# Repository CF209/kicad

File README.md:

<pre>
This repository is for backing up and sharing my PCB designs done in KICAD

ESP8266_Water_Sensor
	- This PCB uses an ESP8266 to make an IOT device with 3 functions:
		1) Reads the resistance from a water level sensor to determine how full a water tank is
		2) Has a header to connect an MPU6050 accelerometer
		3) Can control WS2811 light strips
	- The PCB is powered by 12V and uses a buck converter to step it down to 3.3V for the ESP8266 and the MPU6050
	- The ESP8266 communicates to Home Assistant running on a Raspberry Pi over WIFI
	- Designed to fit in the 1551TFLGY plastic enclosure

ESP32_12v_Relay
	- This PCB uses an ESP32 to make an IOT device
	- The board uses MOSFETs to switch on and off 12V power to up to 4 devices
	- Designed to control lights and solenoids, but can be used for other functions as well
	- MOSFETS can be controlled by hardware PWM outputs from the ESP32
	- The PCB is powered by 12V and uses a buck converter to step it down to 3.3V for the ESP32
	- The ESP32 communicates to Home Assistant running on a Raspberry Pi over WIFI
	- Designed to fit in the 1551TFLGY plastic enclosure
</pre>

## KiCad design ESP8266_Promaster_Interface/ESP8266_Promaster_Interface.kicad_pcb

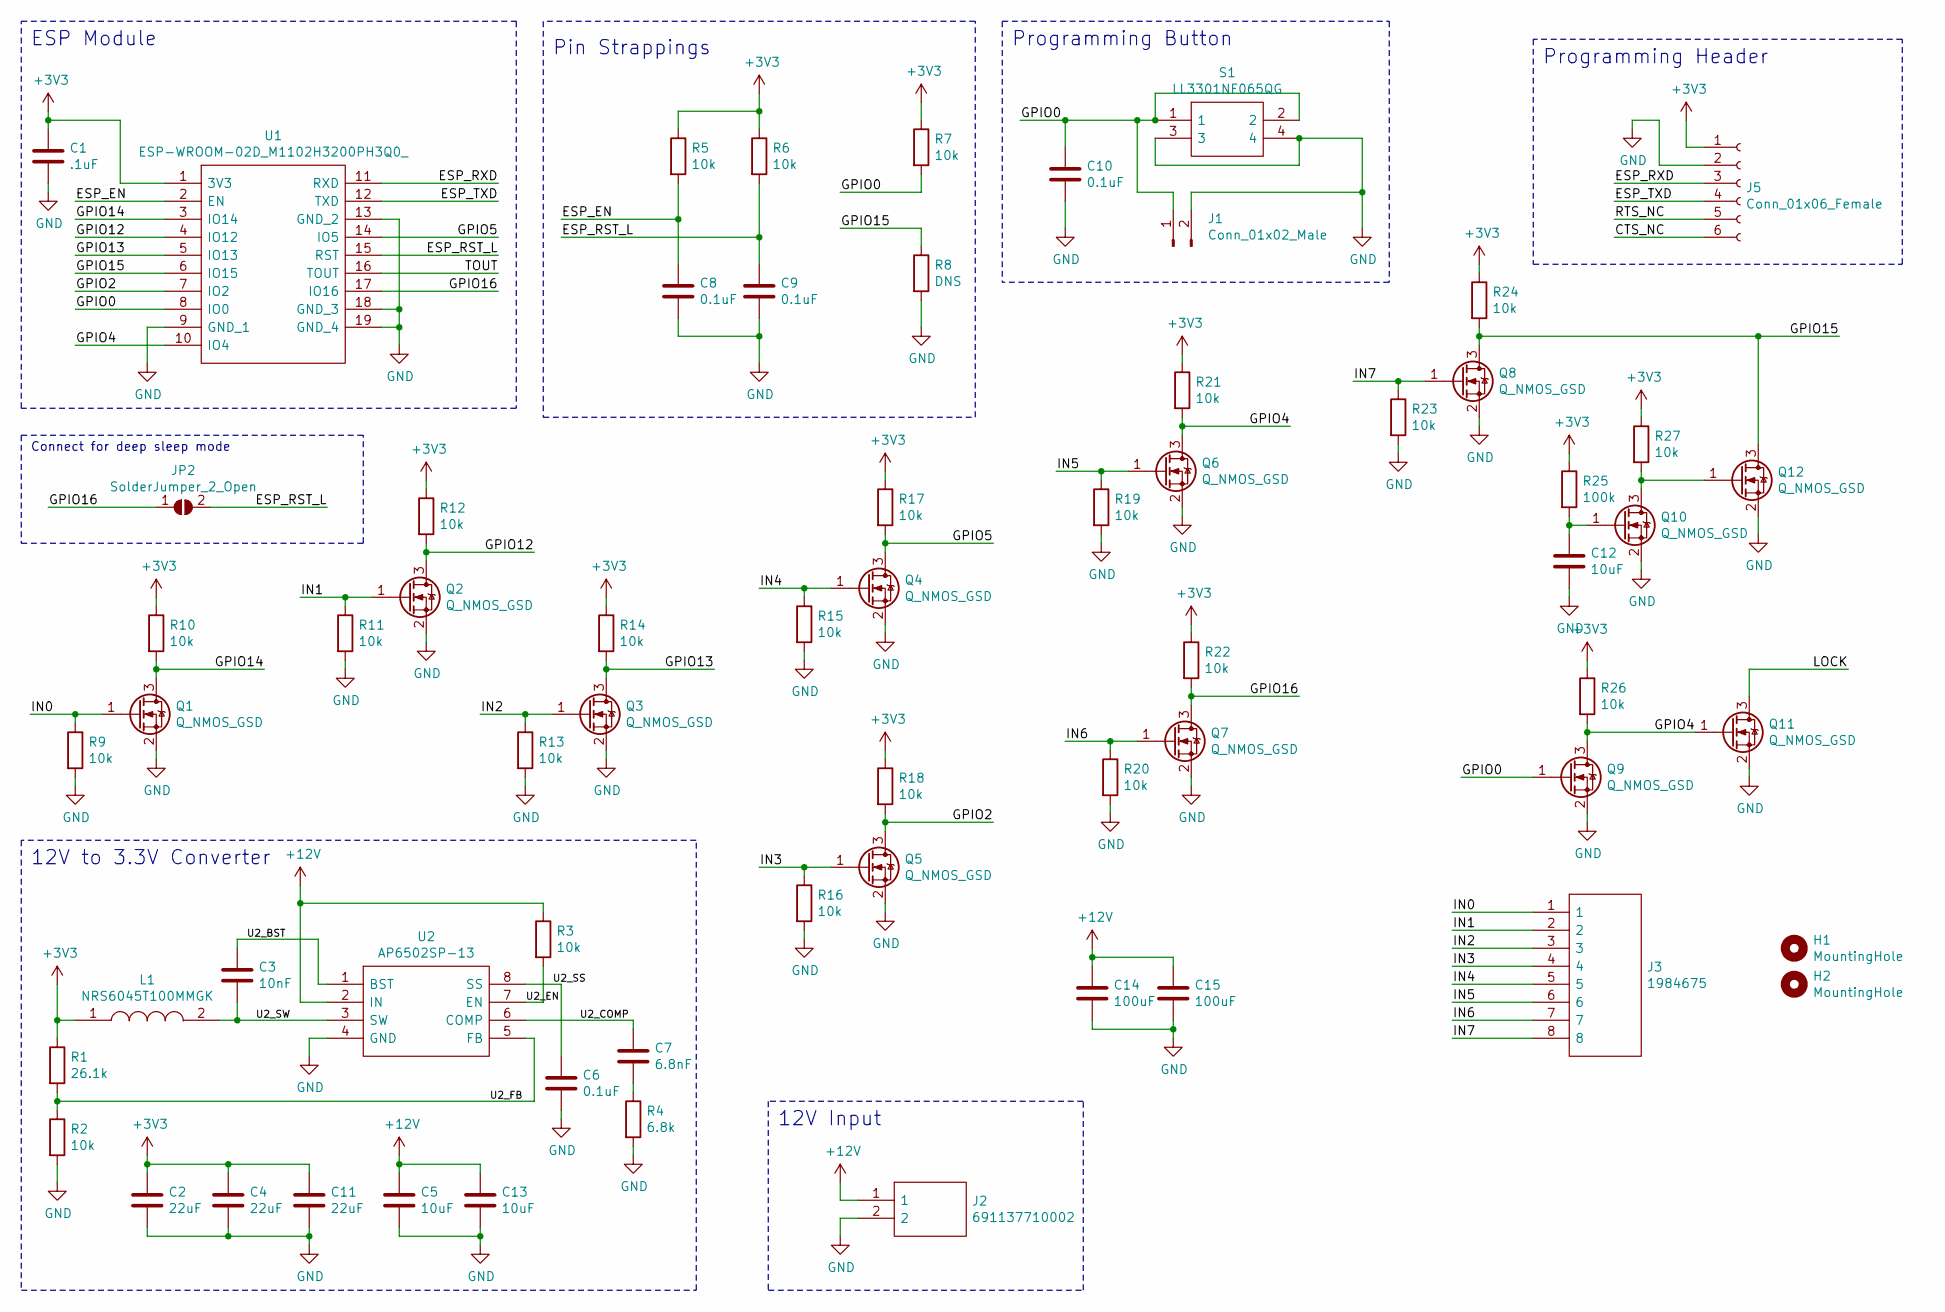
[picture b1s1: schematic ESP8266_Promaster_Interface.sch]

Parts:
C1: .1uF; C_0805_2012Metric_Pad1.18x1.45mm_HandSolder
C2, C4, C11: 22uF; C_0805_2012Metric_Pad1.18x1.45mm_HandSolder
C3: 10nF; C_0805_2012Metric_Pad1.18x1.45mm_HandSolder
C5, C12, C13: 10uF; C_0805_2012Metric_Pad1.18x1.45mm_HandSolder
C6, C8, C9, C10: 0.1uF; C_0805_2012Metric_Pad1.18x1.45mm_HandSolder
C7: 6.8nF; C_0805_2012Metric_Pad1.18x1.45mm_HandSolder
C14, C15: 100uF; CP_Radial_D6.3mm_P2.50mm
H1, H2: MountingHole; MountingHole_2.7mm_M2.5
J1: Conn_01x02_Male; PinHeader_1x02_P2.54mm_Vertical
J2: 691137710002; SHDR2W70P0X500_1X2_1000X750X1160P; Mouser Part Number 710-691137710002
J3: 1984675; Mouser Part Number 651-1984675
J5: Conn_01x06_Female; PinHeader_1x06_P2.54mm_Vertical
JP2: SolderJumper_2_Open; SolderJumper-2_P1.3mm_Open_RoundedPad1.0x1.5mm
L1: NRS6045T100MMGK; NRS6045T101MMGKV; Mouser Part Number 963-NRS6045T100MMGK
Q1, Q2, Q3, Q4, Q5, Q6, Q7, Q8, Q9, Q10, Q11, Q12: Q_NMOS_GSD; SOT-23_Handsoldering
R1: 26.1k; R_0805_2012Metric_Pad1.20x1.40mm_HandSolder
R2, R3, R5, R6, R7, R9, R10, R11, R12, R13, R14, R15, R16, R17, R18, R19, R20, R21, R22, R23, R24, R26, R27: 10k; R_0805_2012Metric_Pad1.20x1.40mm_HandSolder
R4: 6.8k; R_0805_2012Metric_Pad1.20x1.40mm_HandSolder
R8: DNS; R_0805_2012Metric_Pad1.20x1.40mm_HandSolder
R25: 100k; R_0805_2012Metric_Pad1.20x1.40mm_HandSolder
S1: LL3301NF065QG; Mouser Part Number 612-LL3301NF065QG
U1: ESP-WROOM-02D_M1102H3200PH3Q0_; ESPWROOM02DM1102H3200PH3Q0; Mouser Part Number 356-ESPWROOM02D(4MB)
U2: AP6502SP-13; SOIC127P600X150-8N; Mouser Part Number 621-AP6502SP-13

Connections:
+3V3: C1.1, C2.1, C4.1, C11.1, J5.1, L1.1, R1.1, R5.1, R6.1, R7.1, R10.1, R12.1, R14.1, R17.1, R18.1, R21.1, R22.1, R24.1, R25.1, R26.1, R27.1, U1.1 (3V3)
+12V: C5.1, C13.1, C14.1, C15.1, J2.1, R3.1, U2.2 (IN)
/CTS_NC: J5.6
/ESP_EN: C8.1, R5.2, U1.2 (EN)
/ESP_RST_L: C9.1, JP2.2 (B), R6.2, U1.15 (RST)
/ESP_RXD: J5.3, U1.11 (RXD)
/ESP_TXD: J5.4, U1.12 (TXD)
/GPIO0: C10.1, J1.1, Q9.1 (G), R7.2, S1.1, S1.2, U1.8 (IO0)
/GPIO2: Q5.3 (D), R18.2, U1.7 (IO2)
/GPIO4: Q6.3 (D), Q9.3 (D), Q11.1 (G), R21.2, R26.2, U1.10 (IO4)
/GPIO5: Q4.3 (D), R17.2, U1.14 (IO5)
/GPIO12: Q2.3 (D), R12.2, U1.4 (IO12)
/GPIO13: Q3.3 (D), R14.2, U1.5 (IO13)
/GPIO14: Q1.3 (D), R10.2, U1.3 (IO14)
/GPIO15: Q8.3 (D), Q12.3 (D), R8.1, R24.2, U1.6 (IO15)
/GPIO16: JP2.1 (A), Q7.3 (D), R22.2, U1.17 (IO16)
/IN0: J3.1, Q1.1 (G), R9.1
/IN1: J3.2, Q2.1 (G), R11.1
/IN2: J3.3, Q3.1 (G), R13.1
/IN3: J3.4, Q5.1 (G), R16.1
/IN4: J3.5, Q4.1 (G), R15.1
/IN5: J3.6, Q6.1 (G), R19.1
/IN6: J3.7, Q7.1 (G), R20.1
/IN7: J3.8, Q8.1 (G), R23.1
/LOCK: Q11.3 (D)
/RTS_NC: J5.5
/TOUT: U1.16 (TOUT)
/U2_BST: C3.1, U2.1 (BST)
/U2_COMP: C7.1, U2.6 (COMP)
/U2_EN: R3.2, U2.7 (EN)
/U2_FB: R1.2, R2.1, U2.5 (FB)
/U2_SS: C6.1, U2.8 (SS)
/U2_SW: C3.2, L1.2, U2.3 (SW)
GND: C1.2, C2.2, C4.2, C5.2, C6.2, C8.2, C9.2, C10.2, C11.2, C12.2, C13.2, C14.2, C15.2, J1.2, J2.2, J5.2, Q1.2 (S), Q2.2 (S), Q3.2 (S), Q4.2 (S), Q5.2 (S), Q6.2 (S), Q7.2 (S), Q8.2 (S), Q9.2 (S), Q10.2 (S), Q11.2 (S), Q12.2 (S), R2.2, R4.2, R8.2, R9.2, R11.2, R13.2, R15.2, R16.2, R19.2, R20.2, R23.2, S1.3, S1.4, U1.9 (GND_1), U1.13 (GND_2), U1.18 (GND_3), U1.19 (GND_4), U2.4 (GND)
unnamed: C7.2, R4.1
unnamed: C12.1, Q10.1 (G), R25.2
unnamed: Q10.3 (D), Q12.1 (G), R27.2

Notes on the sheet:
Pin Strappings
Programming Button
Programming Header
12V Input
Connect for deep sleep mode
12V to 3.3V Converter
ESP Module

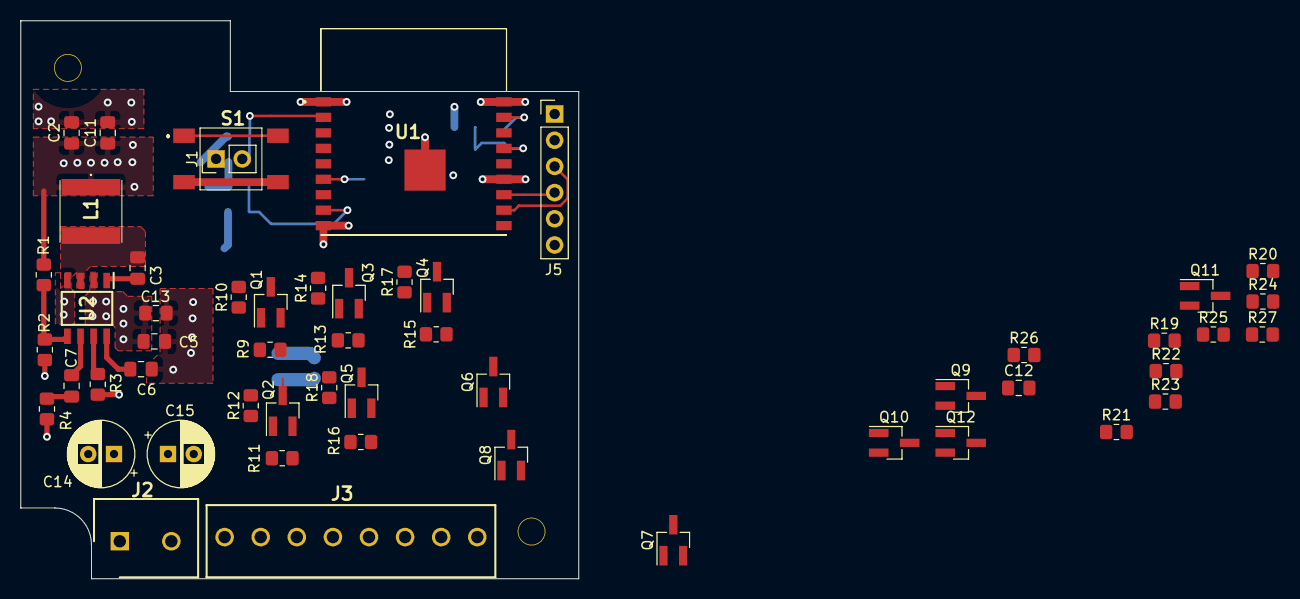
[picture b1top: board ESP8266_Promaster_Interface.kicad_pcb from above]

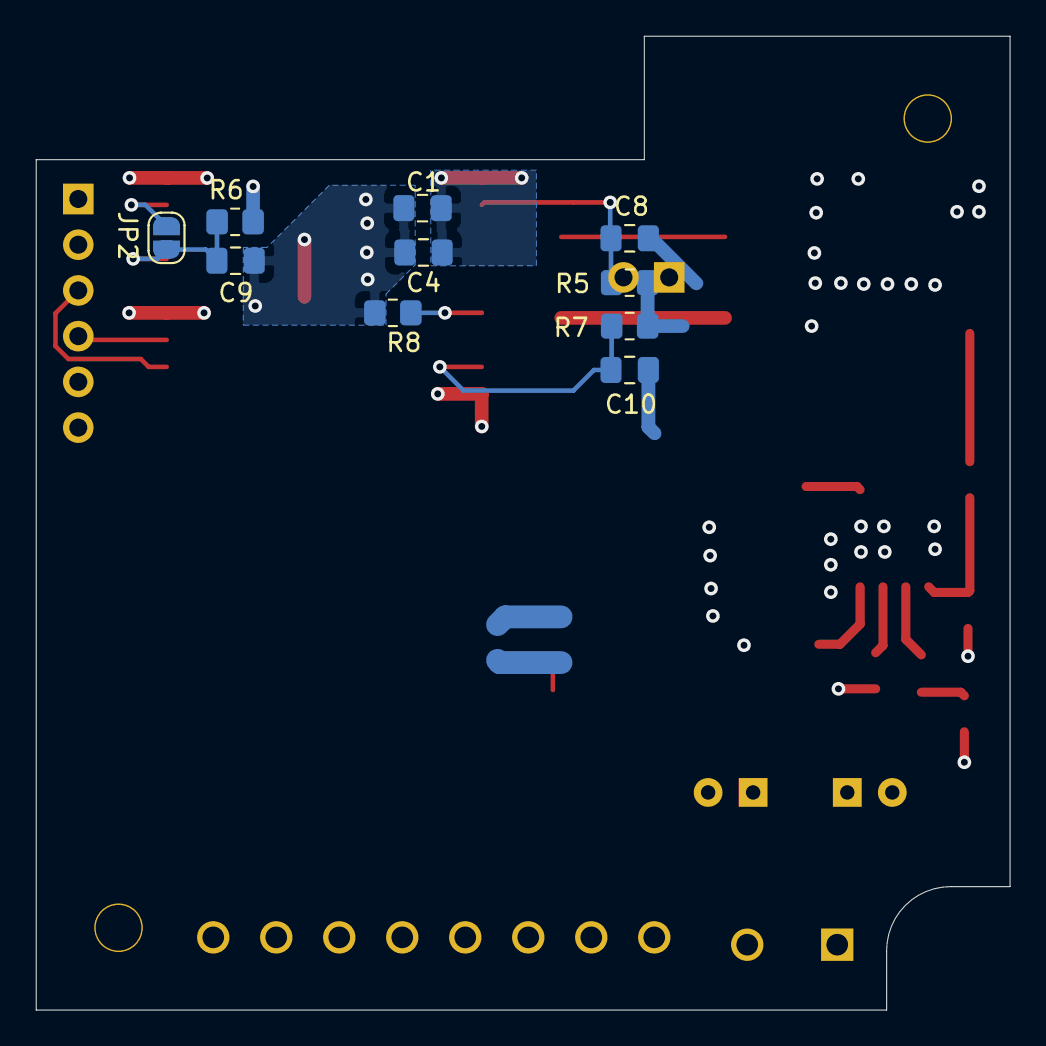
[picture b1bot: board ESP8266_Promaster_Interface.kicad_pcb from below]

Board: 4 copper layers, 54.1 x 54.1 mm, 65 parts (10 on the bottom side), 33 nets.

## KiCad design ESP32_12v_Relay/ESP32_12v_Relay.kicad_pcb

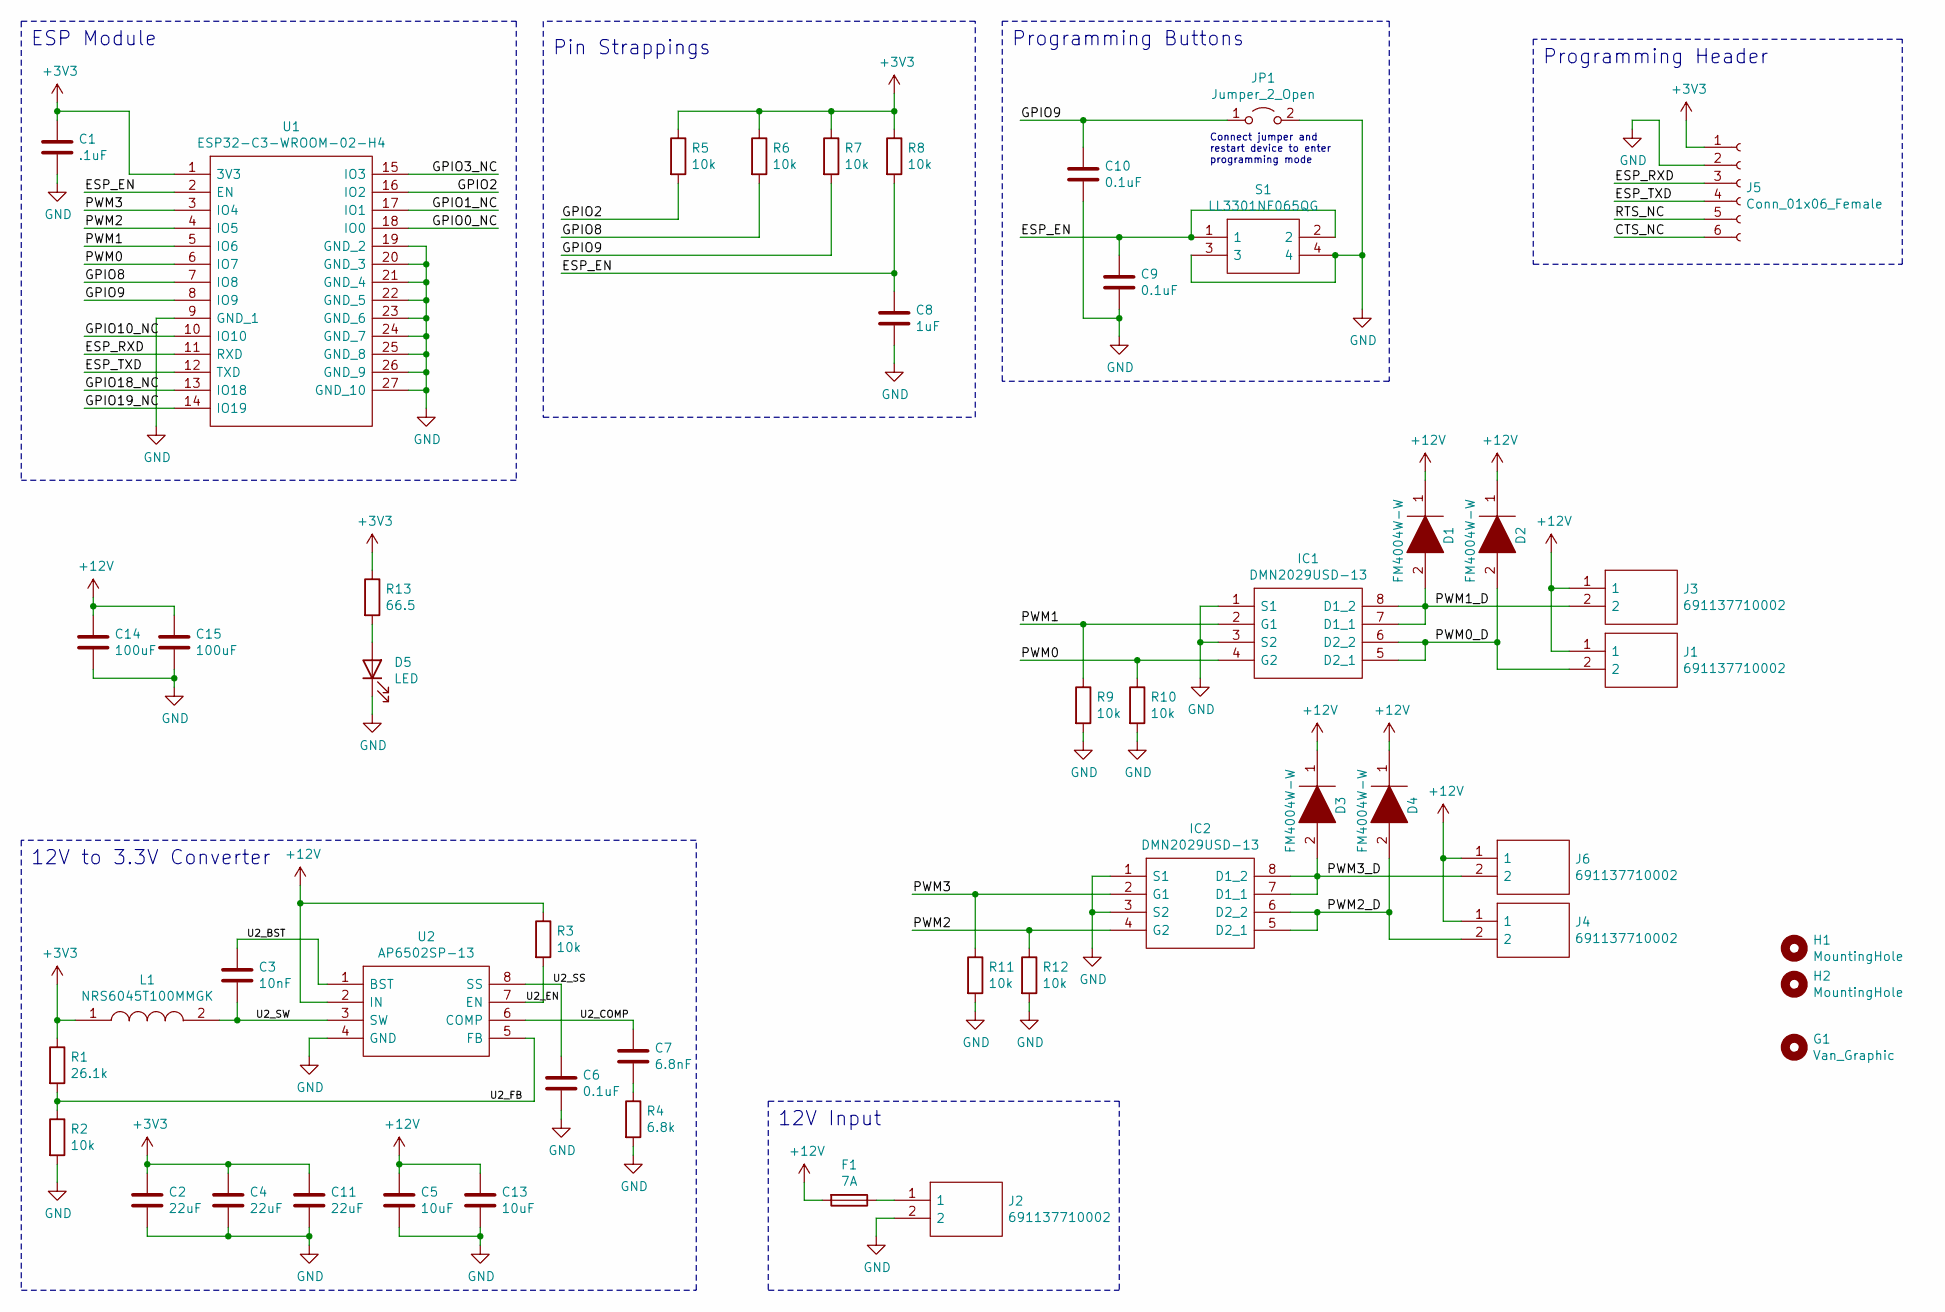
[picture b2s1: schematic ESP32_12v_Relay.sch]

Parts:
C1: .1uF; C_0805_2012Metric_Pad1.18x1.45mm_HandSolder
C2, C4, C11: 22uF; C_0805_2012Metric_Pad1.18x1.45mm_HandSolder
C3: 10nF; C_0805_2012Metric_Pad1.18x1.45mm_HandSolder
C5, C13: 10uF; C_0805_2012Metric_Pad1.18x1.45mm_HandSolder
C6, C9, C10: 0.1uF; C_0805_2012Metric_Pad1.18x1.45mm_HandSolder
C7: 6.8nF; C_0805_2012Metric_Pad1.18x1.45mm_HandSolder
C8: 1uF; C_0805_2012Metric_Pad1.18x1.45mm_HandSolder
C14, C15: 100uF; CP_Radial_D6.3mm_P2.50mm
D1, D2, D3, D4: FM4004W-W; DIOM5025X231N; Mouser Part Number 583-FM4004W-W
D5: LED; LED_0805_2012Metric_Pad1.15x1.40mm_HandSolder
F1: 7A; Fuse_1206_3216Metric_Pad1.42x1.75mm_HandSolder
G1: Van_Graphic; van_pic
H1, H2: MountingHole; MountingHole_2.7mm_M2.5
IC1, IC2: DMN2029USD-13; SOIC127P600X175-8N; Mouser Part Number 621-DMN2029USD-13
J1, J2, J3, J4, J6: 691137710002; SHDR2W70P0X500_1X2_1000X750X1160P; Mouser Part Number 710-691137710002
J5: Conn_01x06_Female; PinHeader_1x06_P2.54mm_Vertical
JP1: Jumper_2_Open; PinHeader_1x02_P2.54mm_Vertical
L1: NRS6045T100MMGK; NRS6045T101MMGKV; Mouser Part Number 963-NRS6045T100MMGK
R1: 26.1k; R_0805_2012Metric_Pad1.20x1.40mm_HandSolder
R2, R3, R5, R6, R7, R8, R9, R10, R11, R12: 10k; R_0805_2012Metric_Pad1.20x1.40mm_HandSolder
R4: 6.8k; R_0805_2012Metric_Pad1.20x1.40mm_HandSolder
R13: 66.5; R_0805_2012Metric_Pad1.20x1.40mm_HandSolder
S1: LL3301NF065QG; Mouser Part Number 612-LL3301NF065QG
U1: ESP32-C3-WROOM-02-H4; ESP32C3WROOM02H4; Mouser Part Number 356-ESP32C3WROOM02H4
U2: AP6502SP-13; SOIC127P600X150-8N; Mouser Part Number 621-AP6502SP-13

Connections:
+3V3: C1.1, C2.1, C4.1, C11.1, J5.1, L1.1, R1.1, R5.1, R6.1, R7.1, R8.1, R13.1, U1.1 (3V3)
+12V: C5.1, C13.1, C14.1, C15.1, D1.1, D2.1, D3.1, D4.1, F1.2, J1.1, J3.1, J4.1, J6.1, R3.1, U2.2 (IN)
/CTS_NC: J5.6
/ESP_EN: C8.1, C9.1, R8.2, S1.1, S1.2, U1.2 (EN)
/ESP_RXD: J5.3, U1.11 (RXD)
/ESP_TXD: J5.4, U1.12 (TXD)
/GPIO0_NC: U1.18 (IO0)
/GPIO1_NC: U1.17 (IO1)
/GPIO2: R5.2, U1.16 (IO2)
/GPIO3_NC: U1.15 (IO3)
/GPIO8: R6.2, U1.7 (IO8)
/GPIO9: C10.1, JP1.1 (A), R7.2, U1.8 (IO9)
/GPIO10_NC: U1.10 (IO10)
/GPIO18_NC: U1.13 (IO18)
/GPIO19_NC: U1.14 (IO19)
/PWM0: IC1.4 (G2), R10.1, U1.6 (IO7)
/PWM0_D: D2.2, IC1.5 (D2_1), IC1.6 (D2_2), J1.2
/PWM1: IC1.2 (G1), R9.1, U1.5 (IO6)
/PWM1_D: D1.2, IC1.7 (D1_1), IC1.8 (D1_2), J3.2
/PWM2: IC2.4 (G2), R12.1, U1.4 (IO5)
/PWM2_D: D4.2, IC2.5 (D2_1), IC2.6 (D2_2), J4.2
/PWM3: IC2.2 (G1), R11.1, U1.3 (IO4)
/PWM3_D: D3.2, IC2.7 (D1_1), IC2.8 (D1_2), J6.2
/RTS_NC: J5.5
/U2_BST: C3.1, U2.1 (BST)
/U2_COMP: C7.1, U2.6 (COMP)
/U2_EN: R3.2, U2.7 (EN)
/U2_FB: R1.2, R2.1, U2.5 (FB)
/U2_SS: C6.1, U2.8 (SS)
/U2_SW: C3.2, L1.2, U2.3 (SW)
GND: C1.2, C2.2, C4.2, C5.2, C6.2, C8.2, C9.2, C10.2, C11.2, C13.2, C14.2, C15.2, D5.1 (K), IC1.1 (S1), IC1.3 (S2), IC2.1 (S1), IC2.3 (S2), J2.2, J5.2, JP1.2 (B), R2.2, R4.2, R9.2, R10.2, R11.2, R12.2, S1.3, S1.4, U1.9 (GND_1), U1.19 (GND_2), U1.20 (GND_3), U1.21 (GND_4), U1.22 (GND_5), U1.23 (GND_6), U1.24 (GND_7), U1.25 (GND_8), U1.26 (GND_9), U1.27 (GND_10), U2.4 (GND)
unnamed: C7.2, R4.1
unnamed: D5.2 (A), R13.2
unnamed: F1.1, J2.1

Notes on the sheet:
Pin Strappings
Programming Buttons
Programming Header
12V Input
12V to 3.3V Converter
ESP Module
Connect jumper and restart device to enter programming mode

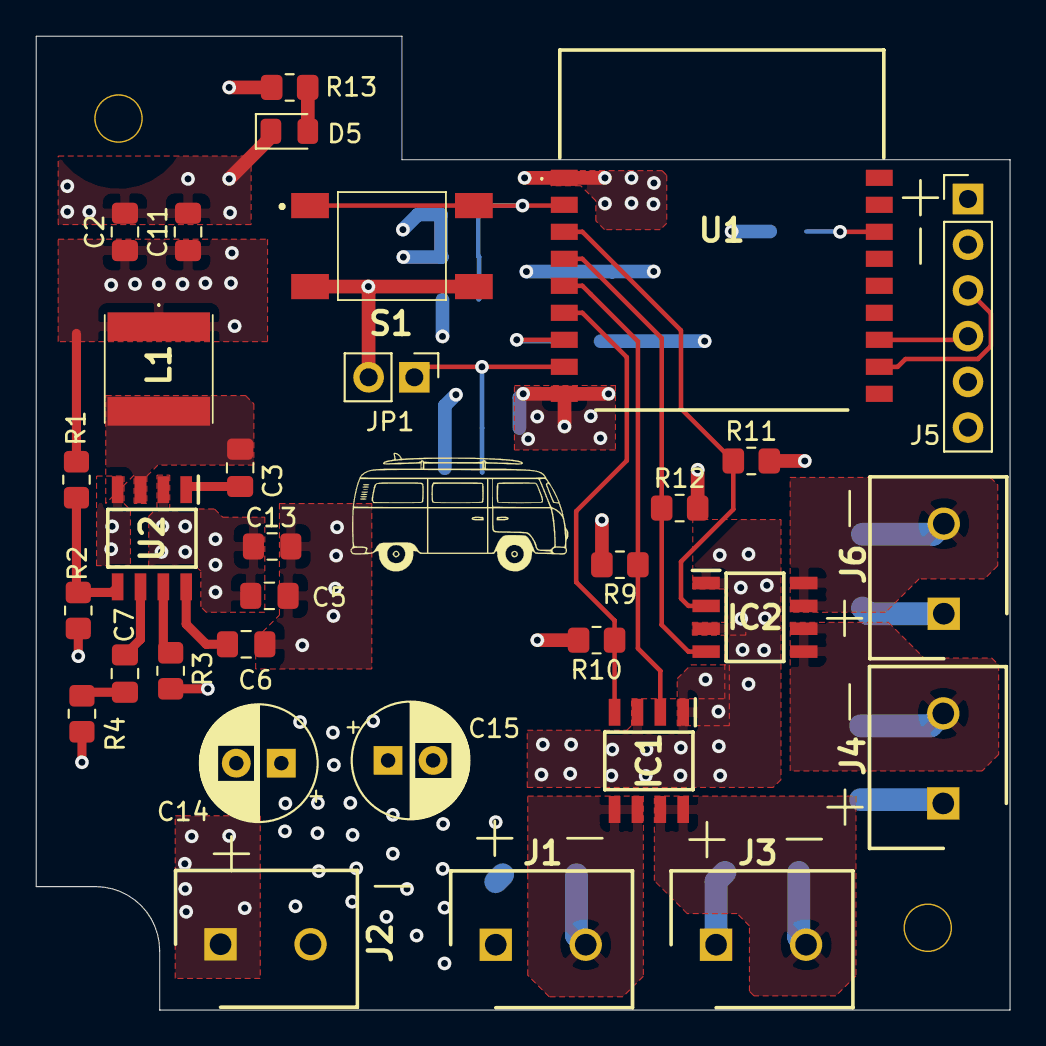
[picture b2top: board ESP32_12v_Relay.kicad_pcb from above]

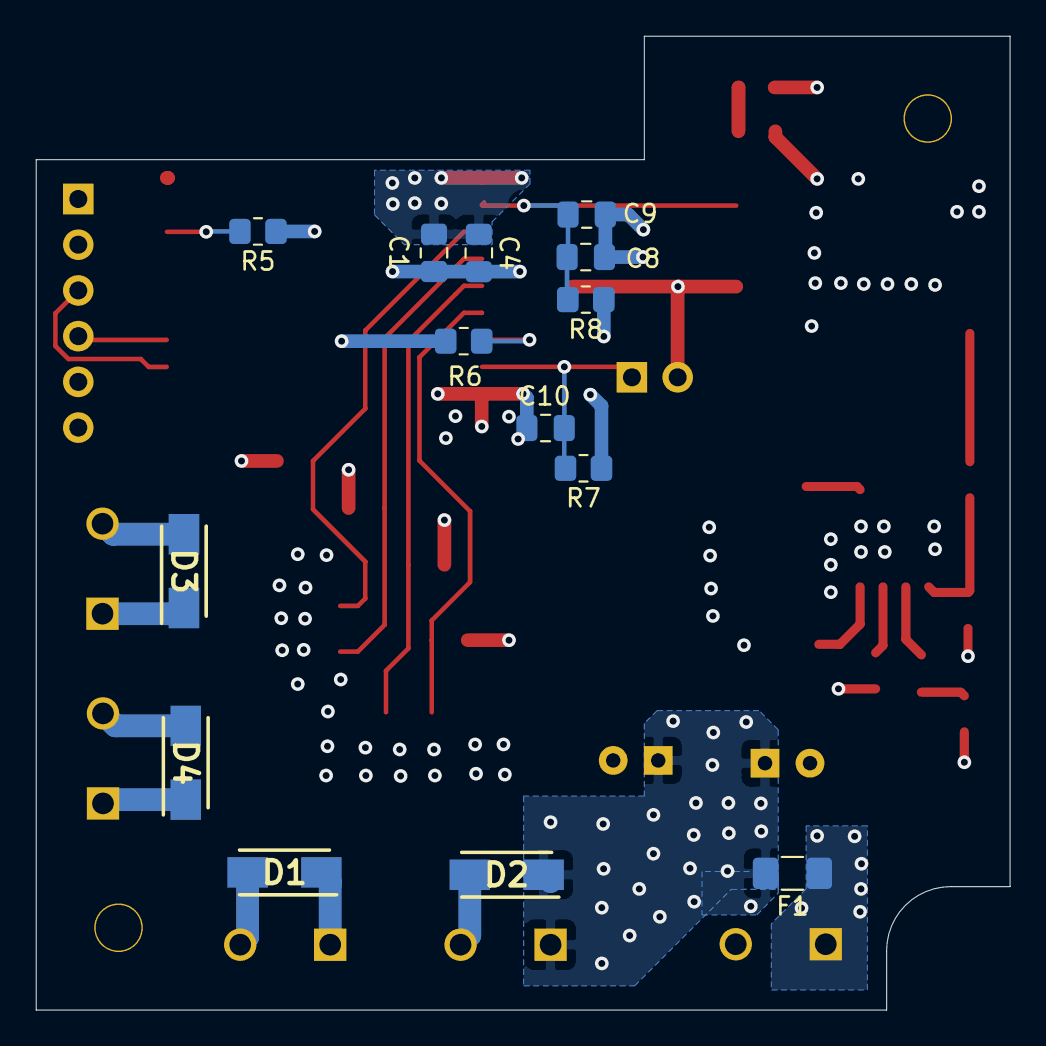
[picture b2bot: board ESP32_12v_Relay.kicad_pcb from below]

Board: 4 copper layers, 54.1 x 54.1 mm, 49 parts (14 on the bottom side), 26 nets.

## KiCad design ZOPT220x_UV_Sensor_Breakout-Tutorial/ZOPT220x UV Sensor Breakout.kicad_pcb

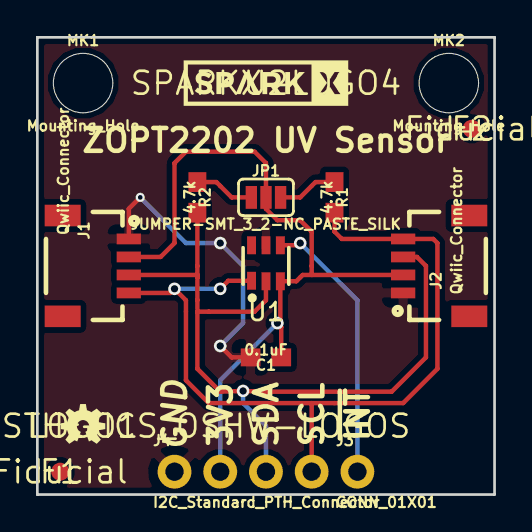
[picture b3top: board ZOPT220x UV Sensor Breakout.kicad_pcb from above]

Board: 2 copper layers, 25.4 x 25.4 mm, 17 parts (1 on the bottom side), 7 nets.

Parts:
C1: 0.1uF; 0603
F1, F2: Fiducial; FIDUCIAL-1X2
J1, J2: Qwiic_Connector; 1X04_1MM_RA
J3: CONN_01X01; 1X01_NO_SILK
J4: I2C_Standard_PTH_Connector; 1X04_NO_SILK
JP1: JUMPER-SMT_3_2-NC_PASTE_SILK; SMT-JUMPER_3_2-NC_PASTE_SILK
LOGO1: SPARKFUN-AESTHETICS_OSHW-LOGOS; OSHW-LOGO-MINI
MK1, MK2: Mounting_Hole; STAND-OFF
R1, R2: 4.7k; 0603
U1: ZOPT220X; ZOPT220x
U2, U3: SPARKX-LOGO4; SPARKX-MEDIUM
U4: CC_LICENSE; CREATIVE_COMMONS

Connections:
+3V3: C1.1, J1.2, J2.2, J4.2, JP1.2, U1.3
GND: C1.2, J1.1, J2.1, J4.1, U1.5
unnamed: JP1.1, R2.1
unnamed: JP1.3, R1.1
SCL: J1.4, J2.4, J4.4, R1.2, U1.1
SDA: J1.3, J2.3, J4.3, R2.2, U1.2
~INT: J3.1, U1.4

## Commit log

2021-08-14 finished routing
2021-08-14 generated gerbers
2021-08-14 edited the silkscreen
2021-08-30 Started 12v relay design
2021-08-31 Finished 12v relay layout
2021-09-01 Added LEDs to 12v relay
2021-11-03 Cleaned up projects
2021-12-14 Fixed missing connection in PCB file

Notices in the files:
parts and their libraries:
Released under the Creative Commons Attribution Share-Alike 4.0 License
https://creativecommons.org/licenses/by-sa/4.0
